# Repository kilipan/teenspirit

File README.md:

# Teenspirit
*I'd rather kiss a Wookiee!*

A not-so-space-invading 18-key ergonomic keyboard with two Piezo-buzzers and a retro-toy looking case.

## BOM
- 1 Teenspirit PCB
- 1 Seeed XIAO compatible controller, like e.g. [Miao](https://github.com/kilipan/miao)
- 9 sot23 diodes (common cathode), look for BAV70
- 18 kailh choc low profile switches
- 18 fitting keycaps

## Firmware
Currently [ZMK firmware](https://github.com/kilipan/zmk-config-teenspirit) and [FAK firmware](https://github.com/kilipan/fak-config/tree/main/keyboards/teenspirit) are available. Neither allows using the buzzers as of yet, but ZMK should soon™️! :)

## Production Files
All files are provided under CERN-OHL-S license.
### PCB
Gerbers for producing the PCB can be found in [`prod/pcb`](https://github.com/kilipan/teenspirit/tree/main/prod/pcb).

### Case
The fantastic case was designed by DizzySkizzo (`dizzyskizzo1337` on discord). Thank you for letting me use and open source this genius design!
Production files available in [`prod/case`](https://github.com/kilipan/teenspirit/tree/main/prod/case).
The case uses threaded heat-inserts of type `M2xL2xOD3` available for example [on Aliexpress](<https://de.aliexpress.com/item/1005006071488810.html>) (make sure to select the correct type! The linked listing has many different options).
Use 7mm screws (6 might also fit, if you want to cut it close).

## Example Keymap
Take this as an inspiration for how typing on this can work very well, not a fixed way to do things! :)

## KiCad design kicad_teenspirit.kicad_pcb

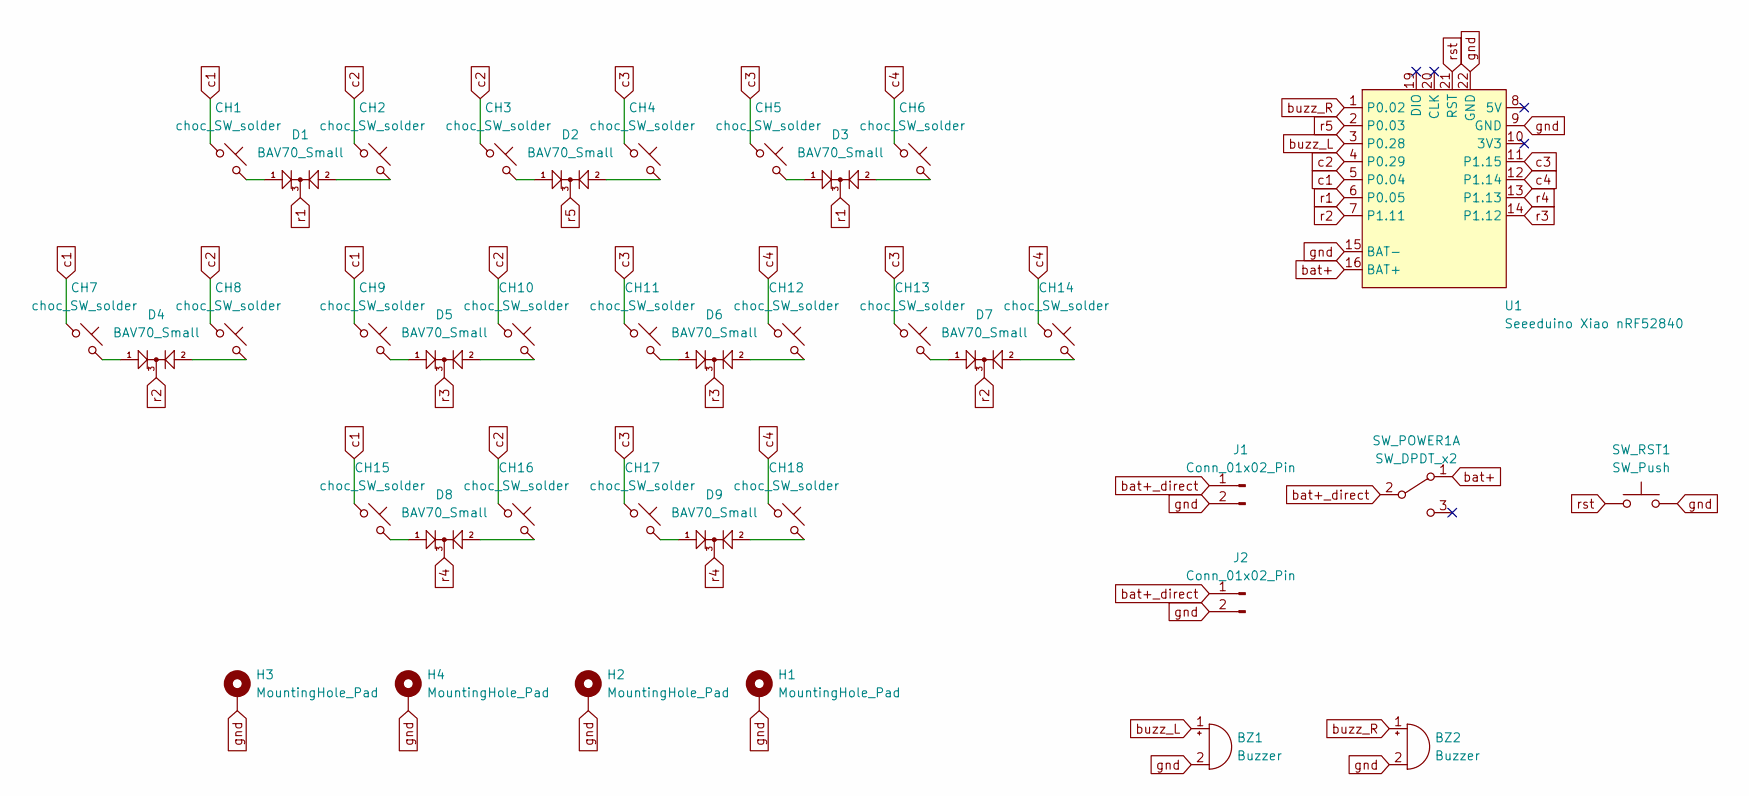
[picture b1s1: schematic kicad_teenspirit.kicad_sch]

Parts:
BZ1, BZ2: Buzzer; Buzzer_Mallory_AST1109MLTRQ
CH1, CH2, CH3, CH4, CH5, CH6, CH7, CH8, CH9, CH10, CH11, CH12, CH13, CH14, CH15, CH16, CH17, CH18: choc_SW_solder; SW_choc_v1_1u
D1, D2, D3, D4, D5, D6, D7, D8, D9: BAV70_Small; apfel_SOT-23_silkless
H1, H2, H3, H4: MountingHole_Pad; MountingHole_2.2mm_M2_Pad_Via_nosilk
J1: Conn_01x02_Pin; JST_GH_SM02B-GHS-TB_1x02-1MP_P1.25mm_Horizontal
J2: Conn_01x02_Pin; PinHeader_1x02_P2.54mm_Vertical
SW_POWER1: SW_DPDT_x2; SW_MSK12C02-HB
SW_RST1: SW_Push; SW_ResetSW
U1: Seeeduino Xiao nRF52840; Xiao_nRF52840_ACH_nosilk_cutout

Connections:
unnamed: CH1.2, D1.1 (A1)
unnamed: CH2.2, D1.2 (A2)
unnamed: CH3.2, D2.1 (A1)
unnamed: CH4.2, D2.2 (A2)
unnamed: CH5.2, D3.1 (A1)
unnamed: CH6.2, D3.2 (A2)
unnamed: CH7.2, D4.1 (A1)
unnamed: CH8.2, D4.2 (A2)
unnamed: CH9.2, D5.1 (A1)
unnamed: CH10.2, D5.2 (A2)
unnamed: CH11.2, D6.1 (A1)
unnamed: CH12.2, D6.2 (A2)
unnamed: CH13.2, D7.1 (A1)
unnamed: CH14.2, D7.2 (A2)
unnamed: CH15.2, D8.1 (A1)
unnamed: CH16.2, D8.2 (A2)
unnamed: CH17.2, D9.1 (A1)
unnamed: CH18.2, D9.2 (A2)
bat+: SW_POWER1.1 (A), U1.16 (BAT+)
bat+_direct: J1.1, J2.1, SW_POWER1.2 (B)
buzz_L: BZ1.1 (-), U1.3 (P0.28)
buzz_R: BZ2.1 (-), U1.1 (P0.02)
c1: CH1.1, CH7.1, CH9.1, CH15.1, U1.5 (P0.04)
c2: CH2.1, CH3.1, CH8.1, CH10.1, CH16.1, U1.4 (P0.29)
c3: CH4.1, CH5.1, CH11.1, CH13.1, CH17.1, U1.11 (P1.15)
c4: CH6.1, CH12.1, CH14.1, CH18.1, U1.12 (P1.14)
gnd: BZ1.2 (+), BZ2.2 (+), H1.1, H2.1, H3.1, H4.1, J1.2, J2.2, SW_RST1.2, U1.9 (GND), U1.15 (BAT-), U1.22 (GND)
r1: D1.3 (K), D3.3 (K), U1.6 (P0.05)
r2: D4.3 (K), D7.3 (K), U1.7 (P1.11)
r3: D5.3 (K), D6.3 (K), U1.14 (P1.12)
r4: D8.3 (K), D9.3 (K), U1.13 (P1.13)
r5: D2.3 (K), U1.2 (P0.03)
rst: SW_RST1.1, U1.21 (RST)

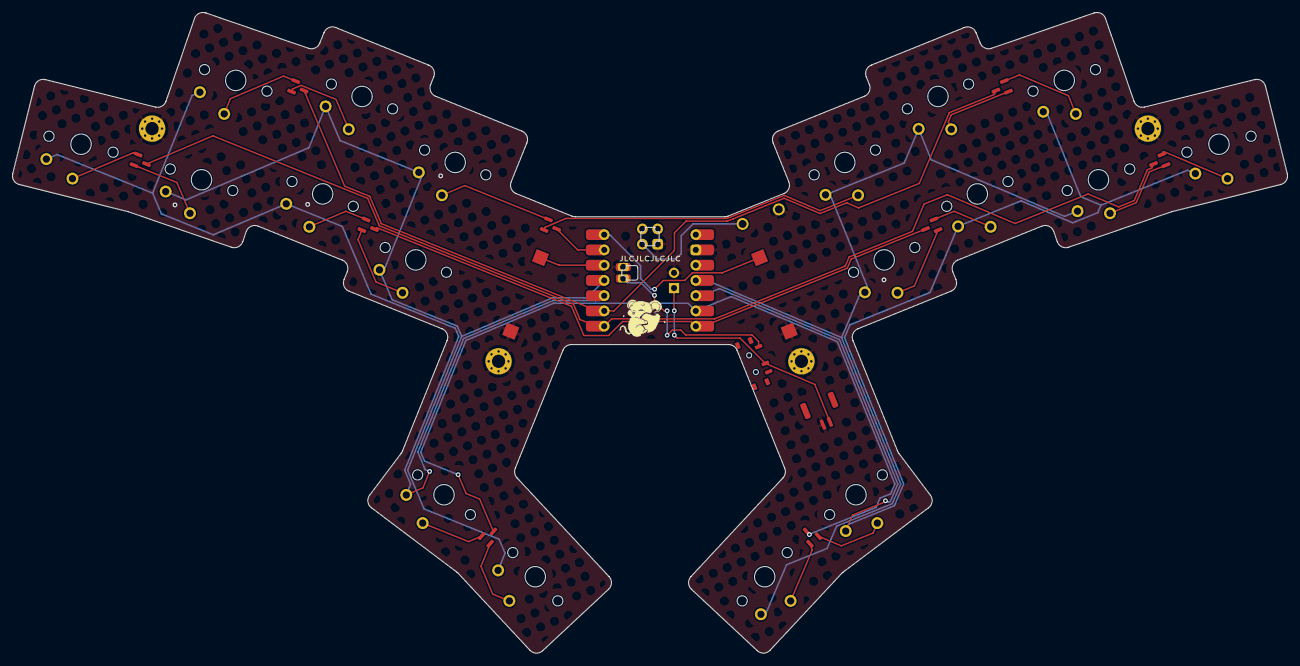
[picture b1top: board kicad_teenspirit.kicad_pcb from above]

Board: 2 copper layers, 212.3 x 106.7 mm, 38 parts (1 on the bottom side), 33 nets.

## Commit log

2024-01-17 fix link
2024-02-28 provide unrar'd case files
2024-06-02 add graphics
2024-06-17 add info on heat-inserts to README.md
2024-06-27 Update README.md with bav70 info
2024-12-18 Add screw length to readme
